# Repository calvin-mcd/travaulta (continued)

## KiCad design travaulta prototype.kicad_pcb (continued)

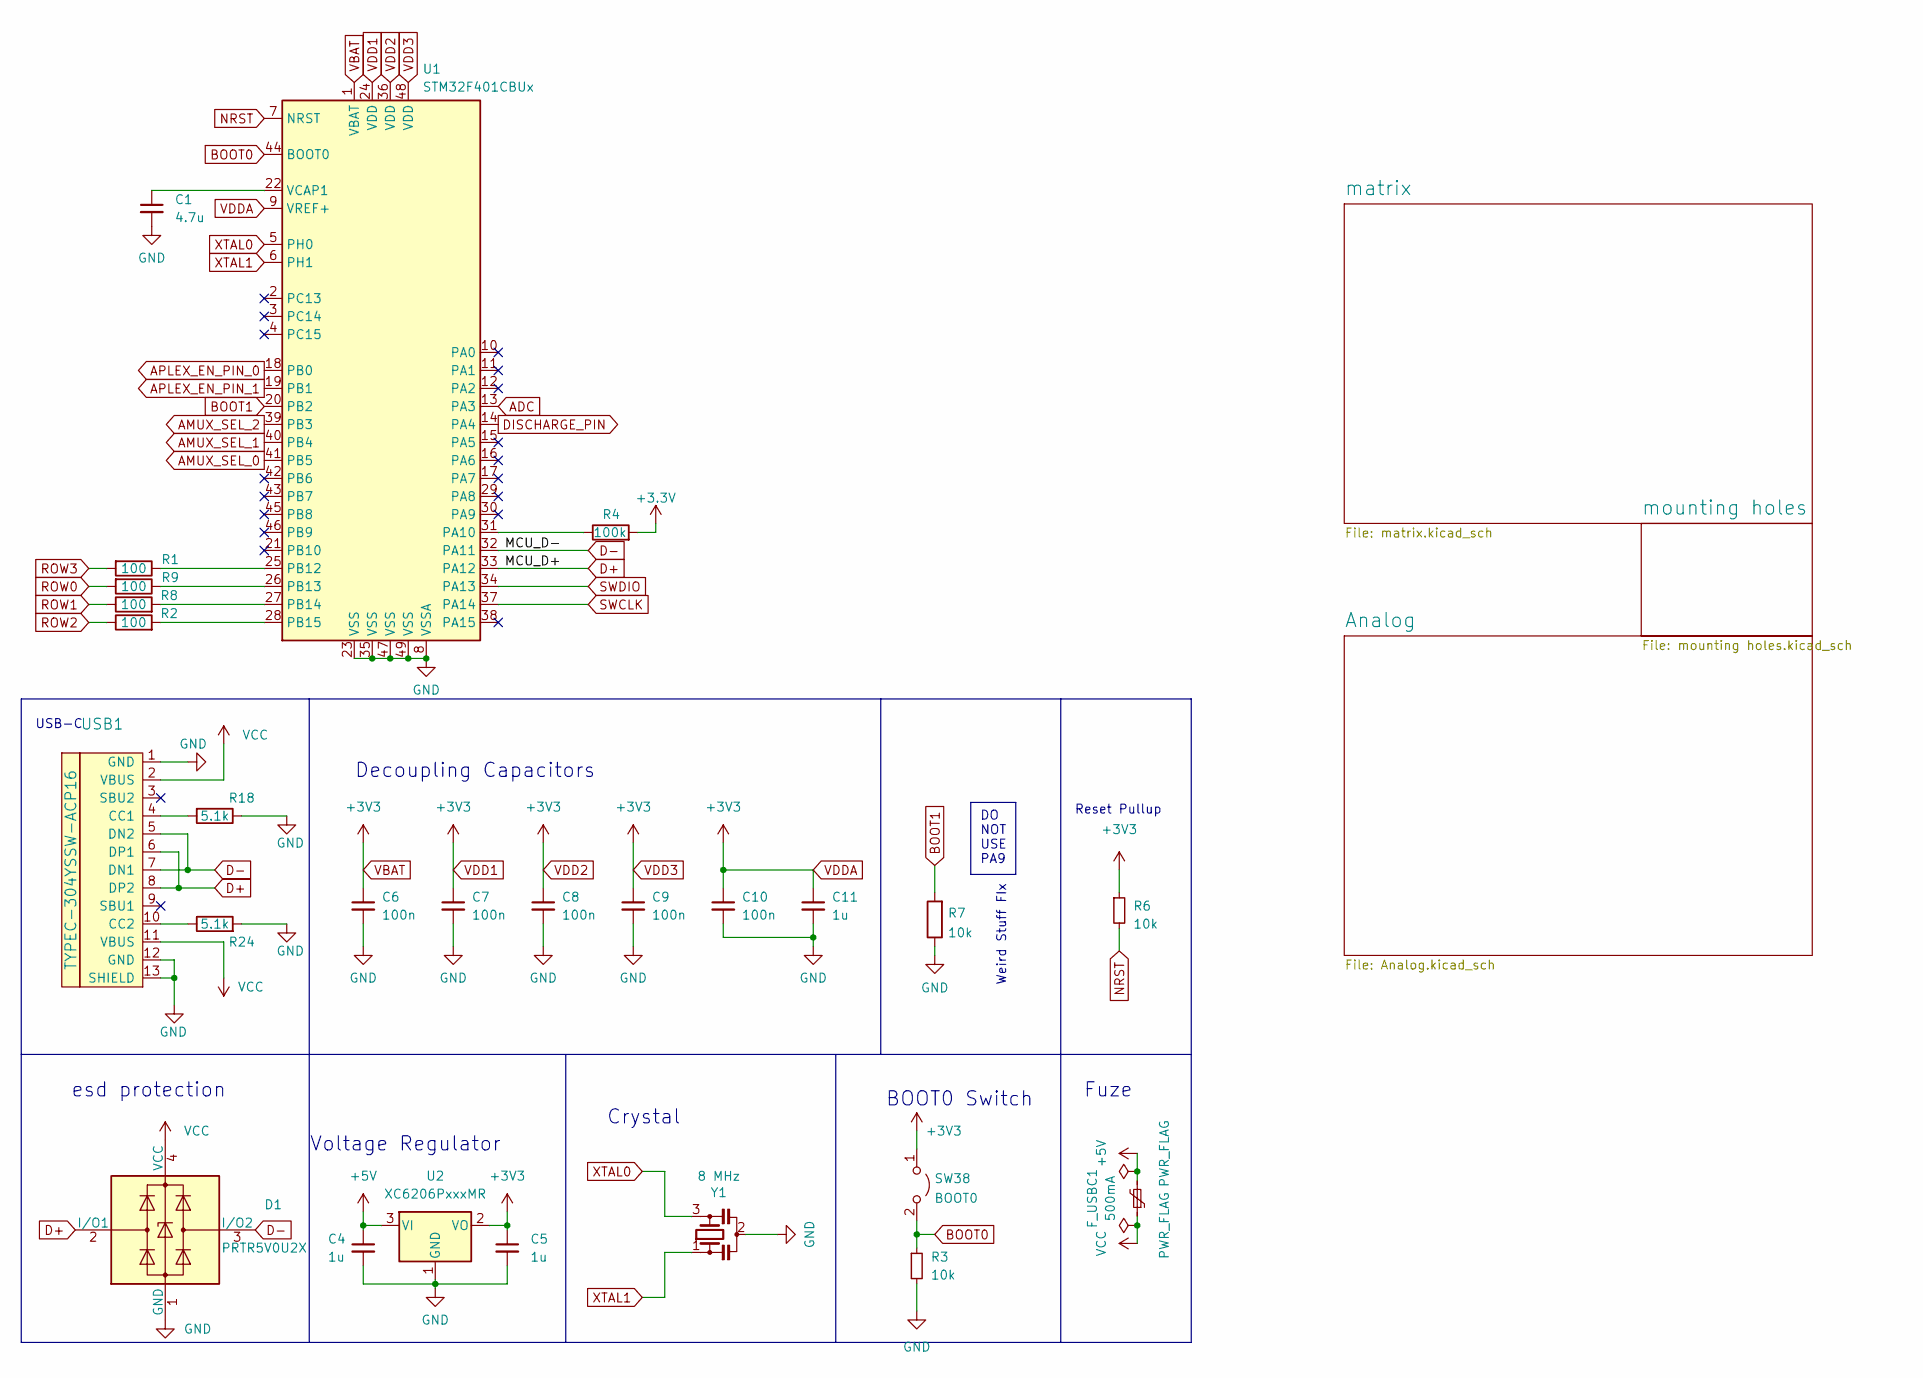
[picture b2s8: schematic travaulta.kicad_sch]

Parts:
C1: 4.7u; C_0402_1005Metric
C4, C5, C11: 1u; C_0402_1005Metric
C6, C7, C8, C9, C10: 100n; C_0402_1005Metric
D1: PRTR5V0U2X; SOT-143
F_USBC1: 500mA; Fuse_1206_3216Metric
R1, R2, R8, R9: 100; R_0402_1005Metric; LCSC C25076
R3, R6: 10k; R_0402_1005Metric
R4: 100k; R_0402_1005Metric; LCSC C25741
R7: 10k; R_0402_1005Metric; LCSC C25744
R18, R24: 5.1k; R_0402_1005Metric; LCSC C25905
SW38: BOOT0; SW_Push_SPST_NO_Alps_SKRK
U1: STM32F401CBUx; QFN-48-1EP_7x7mm_P0.5mm_EP5.6x5.6mm; LCSC C118825
U2: XC6206PxxxMR; SOT-23
USB1: TYPEC-304YSSW-ACP16; LCSC C2840392
Y1: 8 MHz; Resonator_SMD_Murata_CSTxExxV-3Pin_3.0x1.1mm; LCSC C907975

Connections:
+5V: C4.1, F_USBC1.2, U2.3 (VI)
ADC: U1.13 (PA3); also elsewhere on the board
AMUX_SEL_0: U1.41 (PB5); also elsewhere on the board
AMUX_SEL_1: U1.40 (PB4); also elsewhere on the board
AMUX_SEL_2: U1.39 (PB3); also elsewhere on the board
APLEX_EN_PIN_0: U1.18 (PB0); also elsewhere on the board
APLEX_EN_PIN_1: U1.19 (PB1); also elsewhere on the board
APLEX_OUT_PIN_0: U1.14 (PA4); also elsewhere on the board
BOOT0: R3.1, SW38.2 (B), U1.44 (BOOT0)
BOOT1: R7.2, U1.20 (PB2)
D+: D1.2 (I/O1), U1.33 (PA12), USB1.6 (DP1), USB1.8 (DP2)
D-: D1.3 (I/O2), U1.32 (PA11), USB1.5 (DN2), USB1.7 (DN1)
NRST: R6.2, U1.7 (NRST)
unnamed: R4.1, U1.31 (PA10)
unnamed: R9.1, U1.26 (PB13)
unnamed: R8.2, U1.27 (PB14)
unnamed: R2.2, U1.28 (PB15)
unnamed: C1.1, U1.22 (VCAP1)
unnamed: R18.2, USB1.4 (CC1)
unnamed: R24.1, USB1.10 (CC2)
ROW0: R9.2; also elsewhere on the board
ROW1: R8.1; also elsewhere on the board
ROW2: R2.1; also elsewhere on the board
SWCLK: U1.37 (PA14)
SWDIO: U1.34 (PA13)
VCC: D1.4 (VCC), F_USBC1.1, USB1.2 (VBUS), USB1.11 (VBUS)
XTAL0: U1.5 (PH0), Y1.3
XTAL1: U1.6 (PH1), Y1.1

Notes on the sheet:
Weird Stuff FIx
BOOT0 Switch
USB-C
Voltage Regulator
Reset Pullup
esd protection
DO NOT USE PA9
Fuze
Crystal
Decoupling Capacitors

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
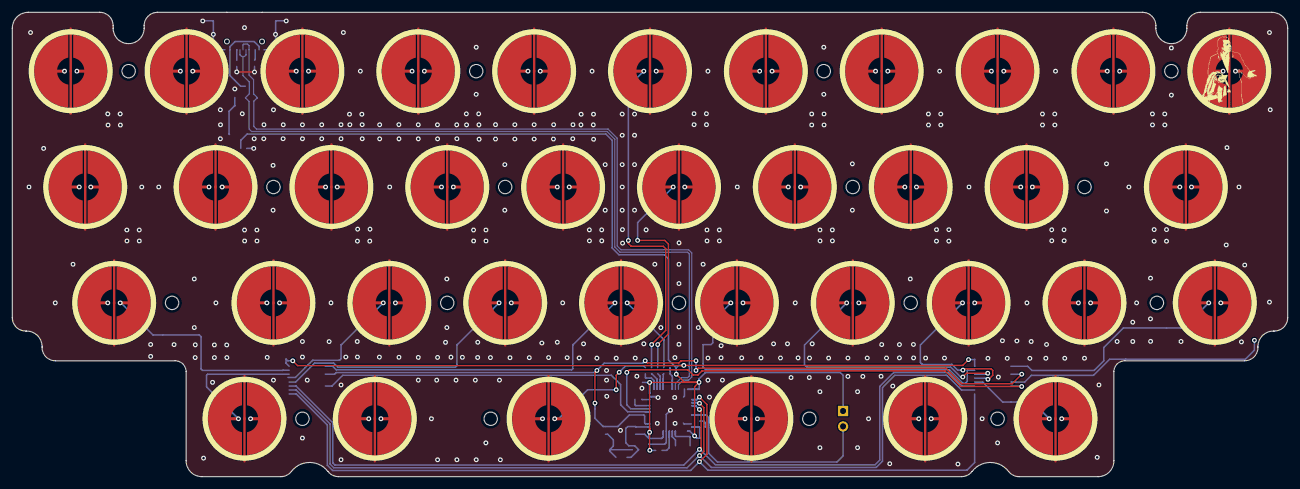
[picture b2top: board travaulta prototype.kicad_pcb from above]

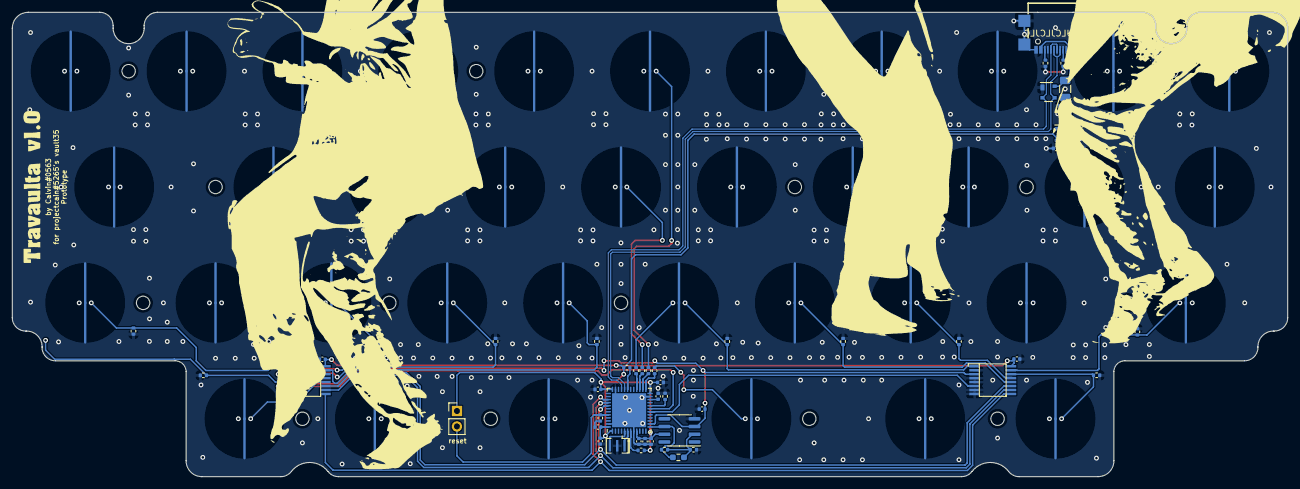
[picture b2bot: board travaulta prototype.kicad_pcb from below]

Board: 4 copper layers, 209.7 x 76.4 mm, 101 parts (47 on the bottom side), 42 nets.

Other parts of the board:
R5: 100k; R_0402_1005Metric
